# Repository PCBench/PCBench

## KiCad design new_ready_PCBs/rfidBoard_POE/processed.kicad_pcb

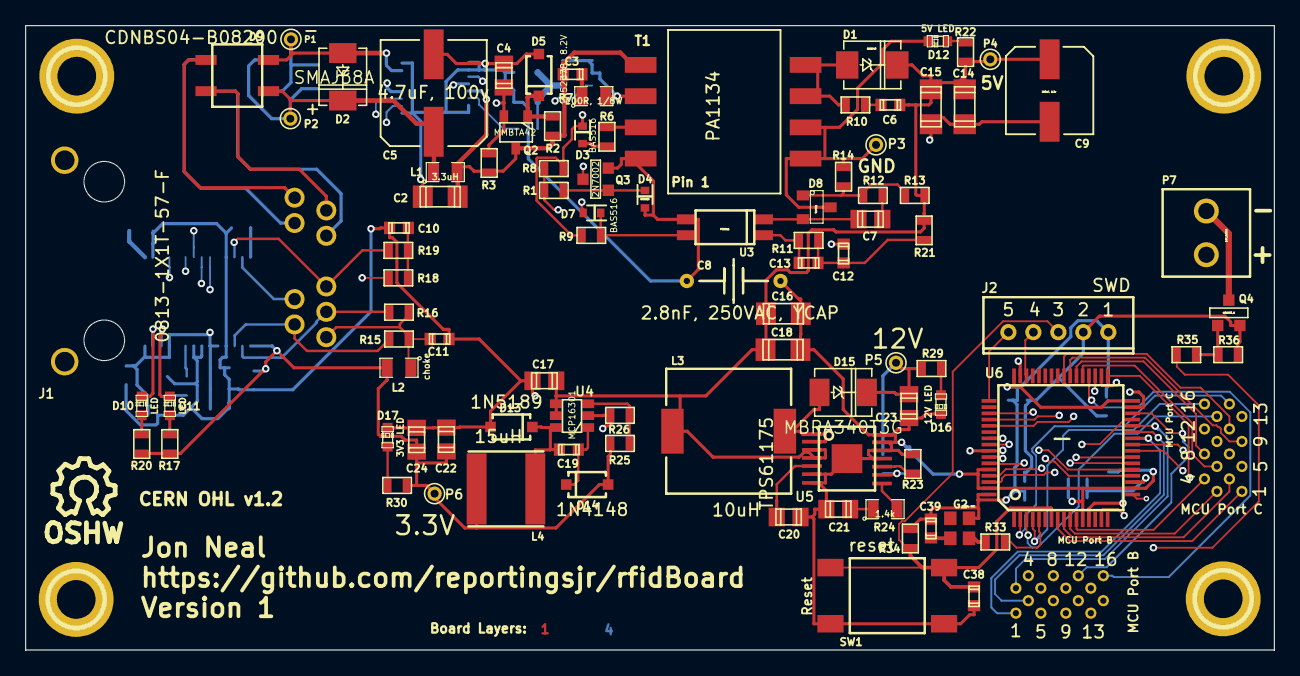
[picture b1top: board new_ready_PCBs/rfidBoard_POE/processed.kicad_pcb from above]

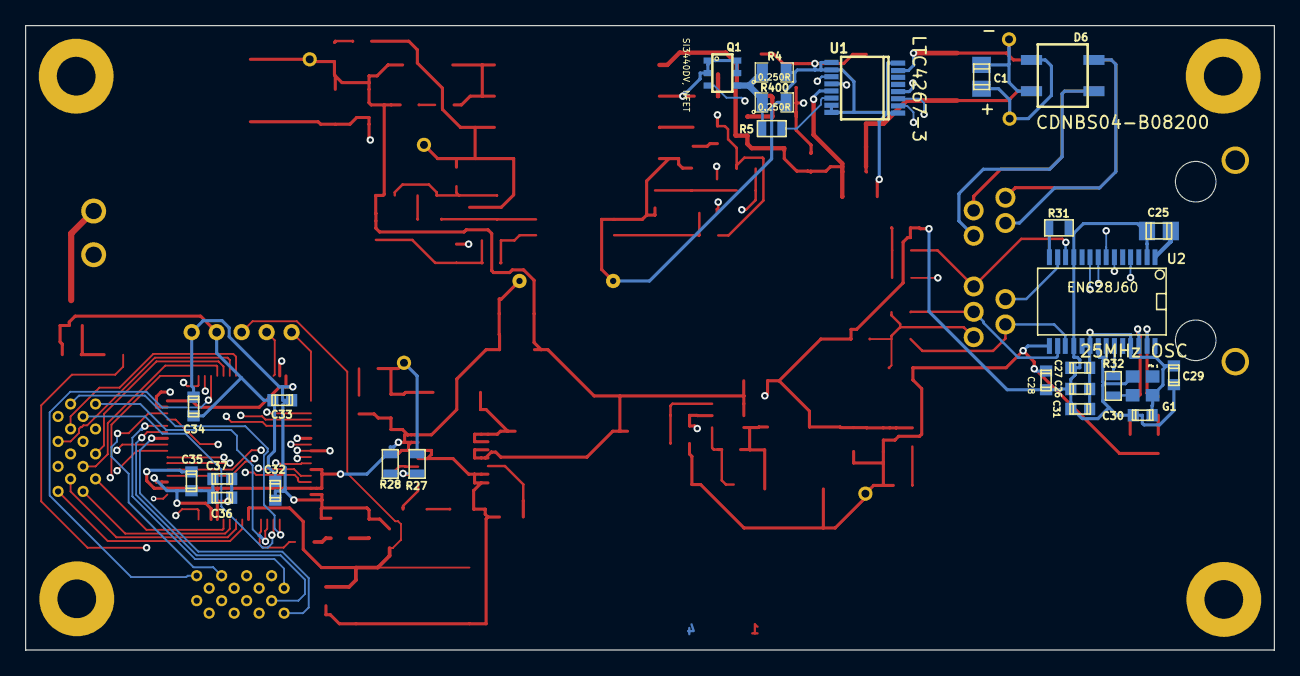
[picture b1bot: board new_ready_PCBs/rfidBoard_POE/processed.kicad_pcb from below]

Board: 4 copper layers, 100.0 x 50.0 mm, 127 parts (26 on the bottom side), 104 nets.

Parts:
1PIN, 1PIN_2, 1PIN_3, 1PIN_4: P***; 1pin
C1: 0.1uF, 100V, X7R; c_0805
C2: 1uF, 100V; c_1206
C3: 68pF, 200V; c_0603
C4: 4.7uF, 10V; c_0805
C5: 4.7uF, 100v; EEE-2AA4R7UP
C6: 470pF; c_0603
C7: 27nF; c_0805
C8: 2.8nF, 250VAC, YCAP; kemet_C900
C9: 220uF, 6.3v; EEE-FK0J221P
C10, C11: 10nF; c_0603
C12, C31, C37: 1uF; c_0603
C13: 33nF; c_0603
C14, C15: 100uF, 6.3V, X5R; c_1206
C16, C18: 10uF; c_1206
C17, C22, C24, C25: 10uF; c_0805
C19, C26, C27, C28, C29, C30, C32, C33, C34, C35, C36, C38, C39: 100nF; c_0603
C20: 47nF; c_0805
C21: 180nF; c_0805
C23: 22uF; c_0805
D1: SMB540; DO-214-AA_SMB
D2: SMAJ58A; DO-214-AC_SMA
D3, D4, D7: BAS516; SOD-523
D5: 1N5237B, 8.2V; SOD-123
D6, D9: CDNBS04-B08200; CDNBS04
D8: TLV431; SOT-23
D10, D11: LED; LED-0603
D12: 5V LED; LED-0603
D13: 1N5189; SOD-123
D14: 1N4148; SOD-123
D15: MBRA340T3G; DO-214-AC_SMA
D16: 12V LED; LED-0603
D17: 3V3 LED; LED-0603
G1: 25MHz OSC; Si501_2.5x2
G2: 24MHz OSC; Si501_2.5x2
J1: 0813-1X1T-57-F
J2: SWD; JST_PH_5pin
J3: MCU Port B; 16_pin_breakout
J4: MCU Port C; 16_pin_breakout
L1: 3.3uH; SMD-0805
L2: choke; SMD-0805
L3: 10uH; SRU1048
L4: 15uH; NR6028
P1: PoE-; PINTST
P2: PoE+; PINTST
P3: GND; PINTST
P4: +5V; PINTST
P5: +12V; PINTST
P6: +3V3; PINTST
P7: 12V_Switch; SIL2-3.5mm
Q1: SI3440DV, NFET; TSOP-6
Q2: MMBTA42; SOT-23_Inv2
Q3: 2N7002; SOT-23-GDS
Q4: MOSFET_N; SOT-23-GDS
R1, R26, R29, R36: 10k; SMD-0603
R2, R3: 220K; SMD-0603
R4, R400: 0.250R; SMD-0805
R5: 4.7K; SMD-0603
R6: 510R; SMD-0603
R7: 100R, 1/8W; SMD-0805
R8: 100k; SMD-0603
R9: 6.8k; SMD-0603
R10: 10R; SMD-0603
R11, R17, R20: 1k; SMD-0603
R12: 47k; SMD-0603
R13: 100k, 1%; SMD-0603
R14: 33.2k; SMD-0603
R15, R16, R18, R19: 49R9; SMD-0603
R21, R35: 470R; SMD-0603
R22, R30: 2.8k; SMD-0603
R23: 226k; SMD-0603
R24: 1.4k; SMD-0805
R25: 31.2k; SMD-0603
R27: 143k; SMD-0603
R28: 16.2k; SMD-0603
R31: 2.32k; SMD-0603
R32, R33: 24.9; SMD-0603
R34: 4.7k; SMD-0603
SW1: reset; TE-Switch-FSM-JSM
SYM: Symbol_OSHW-Logo_SilkScreen_07Jul2012; Symbol_OSHW-Logo_SilkScreen
T1: PA1134
U1: LTC4267-3; SSOP-16
U2: ENC28J60; SSOP-28
U3: PS2811; SSOP-4
U4: MCP16301; SOT-23-6
U5: TPS61175; HTSSOP-14-1EP
U6: STM32F100RC; LQFP64

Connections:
3V3: C22.1, C24.1, C26.1, C27.1, C28.1, C29.1, C30.2, C31.1, C32.1, C33.1, C34.1, C35.1, C36.1, C37.1, C39.2, D14.1, G1.4, G2.4, J2.1, L2.2, L4.2, P6.1, R17.2, R20.2, R25.1, R30.1, R34.2, U2.15, U2.19, U2.20, U2.25, U2.28, U6.13, U6.19, U6.32, U6.48, U6.64
5VPoE: C6.1, C9.1, C14.1, C15.1, C16.1, C17.1, C18.1, D1.2, L3.1, P4.1, R13.1, R21.2, R22.1, U4.4, U4.5, U5.3, U5.4
12V: C23.1, D15.2, P5.1, P7.1, R27.1, R29.1
/12VSwitch: R35.2, U6.15
/Ethernet+: D6.3, J1.10
/Ethernet-: D6.2, J1.5
/EthernetCS: U2.9, U6.20
/EthernetINT: U2.4, U6.17
/EthernetSCK: U2.8, U6.21
/EthernetSI: U2.7, U6.23
/EthernetSO: U2.6, U6.22
/EthernetSpare+: D9.3, J1.6
/EthernetSpare-: D9.2, J1.11
/PB0: J3.1, U6.26
/PB1: J3.2, U6.27
/PB2: J3.3, U6.28
/PB3: J3.4, U6.55
/PB4: J3.5, U6.56
/PB5: J3.6, U6.57
/PB6: J3.7, U6.58
/PB7: J3.8, U6.59
/PB8: J3.9, U6.61
/PB9: J3.10, U6.62
/PB10: J3.11, U6.29
/PB11: J3.12, U6.30
/PB12: J3.13, U6.33
/PB13: J3.14, U6.34
/PB14: J3.15, U6.35
/PB15: J3.16, U6.36
/PC0: J4.1, U6.8
/PC1: J4.2, U6.9
/PC2: J4.3, U6.10
/PC3: J4.4, U6.11
/PC4: J4.5, U6.24
/PC5: J4.6, U6.25
/PC6: J4.7, U6.37
/PC7: J4.8, U6.38
/PC8: J4.9, U6.39
/PC9: J4.10, U6.40
/PC10: J4.11, U6.51
/PC11: J4.12, U6.52
/PC12: J4.13, U6.53
/PC13: J4.14, U6.2
/PC14: J4.15, U6.3
/PC15: J4.16, U6.4
/PVcc: C4.2, D3.2, Q2.1, R3.2, R8.2, R9.1, U1.4
/TPIN+: J1.2, R18.2, U2.13
/TPIN-: J1.9, R19.2, U2.12
/TPOUT+: J1.1, R15.2, U2.17
/TPOUT-: J1.8, R16.2, U2.16
/nRST: C38.2, J2.3, R34.1, SW1.1, SW1.2, U6.7
GND: C8.2, C9.2, C10.2, C11.2, C12.2, C14.2, C15.2, C16.2, C17.2, C18.2, C20.2, C21.2, C22.2, C23.2, C24.2, C25.1, C26.2, C27.2, C28.2, C29.2, C30.1, C31.2, C32.2, C33.2, C34.2, C35.2, C36.2, C37.2, C38.1, D8.3, D12.2, D13.1, D16.2, D17.2, G1.2, J2.2, P3.1, Q4.S, R14.2, R23.2, R26.2, R28.2, R31.1, R36.2, SW1.3, SW1.4, T1.7, T1.8, U2.2, U2.11, U2.18, U2.21, U2.22, U4.2, U5.6, U5.7, U5.11, U5.12, U5.13, U5.14, U5.15, U6.12, U6.18, U6.31, U6.47, U6.60, U6.63
GNDA: C2.2, C4.1, C5.2, C8.1, D4.1, D5.1, J1.12, Q3.S, R4.2, R400.2, T1.1, U1.1, U1.8, U1.9, U1.10, U1.15, U1.16, U3.3
unnamed: C1.1, C5.1, D2.2, D6.1, D9.1, L1.1, P2.1
unnamed: C1.2, D2.1, D6.4, D9.4, P1.1, U1.7, U1.12
unnamed: C2.1, C3.1, L1.2, Q2.3, R2.1, R3.1, T1.4, U1.13
unnamed: C3.2, R7.1
unnamed: C6.2, R10.2
unnamed: C7.1, R12.1
unnamed: C7.2, D8.2, U3.2
unnamed: C10.1, R18.1, R19.1
unnamed: C11.1, J1.7, L2.1, R15.1, R16.1
unnamed: C12.1, C13.1, R11.1, R21.1
unnamed: C13.2, R11.2, U3.1
unnamed: C19.1, D14.2, U4.1
unnamed: C19.2, D13.2, L4.1, U4.6
unnamed: C20.1, U5.5
unnamed: C21.1, R24.1
unnamed: C25.2, U2.1
unnamed: C39.1, G2.2
unnamed: D1.1, R10.1, T1.5, T1.6
unnamed: D3.1, R6.1
unnamed: D4.2, Q3.G, R1.2
unnamed: D5.2, Q2.2, R2.2
unnamed: D7.1, Q3.D, U1.2
unnamed: D7.2, R9.2, U3.4
unnamed: D8.1, R12.2, R13.2, R14.1
unnamed: D10.1, R20.1
unnamed: D10.2, U2.27
unnamed: D11.1, R17.1
unnamed: D11.2, U2.26
unnamed: D12.1, R22.2
unnamed: D15.1, L3.2, U5.1, U5.2
unnamed: D16.1, R29.2
unnamed: D17.1, R30.2
unnamed: G1.3, R32.1
unnamed: G2.3, R33.1
unnamed: J2.4, U6.46
unnamed: J2.5, U6.49
unnamed: P7.2, Q4.D
unnamed: Q1.1, Q1.2, Q1.5, Q1.6, R7.2, T1.3
unnamed: Q1.3, U1.3
unnamed: Q1.4, R4.1, R5.2, R400.1
unnamed: Q4.G, R35.1, R36.1
unnamed: R1.1, R8.1, U1.11
unnamed: R5.1, U1.14
unnamed: R6.2, T1.2
unnamed: R23.1, U5.10
unnamed: R24.2, U5.8
unnamed: R25.2, R26.1, U4.3
unnamed: R27.2, R28.1, U5.9
unnamed: R31.2, U2.14
unnamed: R32.2, U2.23
unnamed: R33.2, U6.5

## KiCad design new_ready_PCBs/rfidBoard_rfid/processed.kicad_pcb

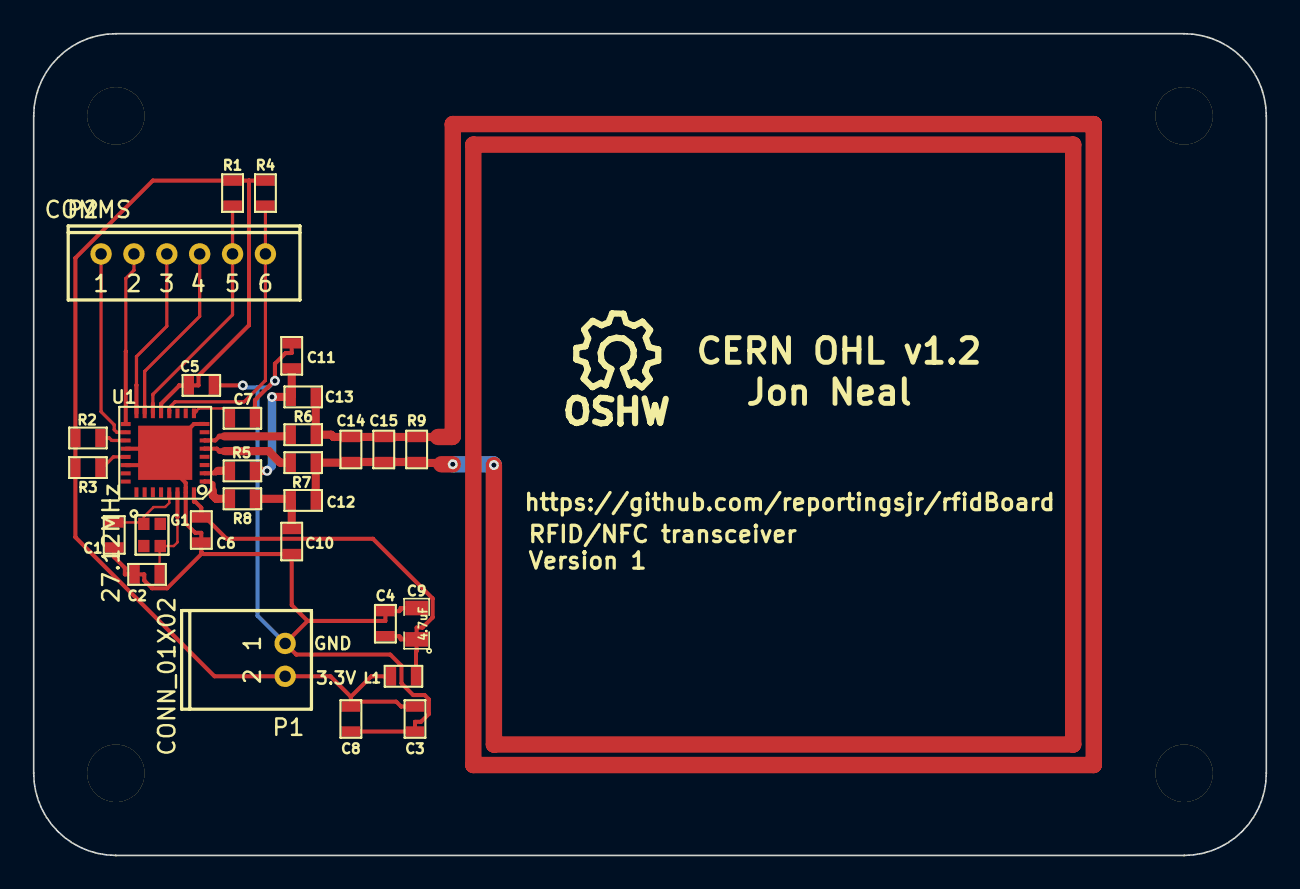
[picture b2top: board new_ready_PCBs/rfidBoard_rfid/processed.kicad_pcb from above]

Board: 2 copper layers, 75.0 x 50.0 mm, 34 parts (0 on the bottom side), 21 nets.

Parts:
C1, C2: 4pF; SMD-0603
C3, C4: 10nF; SMD-0603
C5, C6: 100nF; SMD-0603
C7: 1nF; SMD-0603
C8: 1uF; SMD-0603
C9: 4.7uF; SMD-0805
C10, C11: open; SMD-0603
C12, C13: 150pF; SMD-0603
C14: 220pF; SMD-0603
C15: 15pF; SMD-0603
G1: 27.12MHz; 2x1.6_crystal
L1: tx_3v3_choke; SMD-0603
MH: MountingHole_3-5mm_RevA_Date21Jun2010; MountingHole_3-5mm
MH_2, MH_3, MH_4: MountingHole_3-5mm_RevA_Date21Jun2010; MountingHole_3-5mm
P1: CONN_01X02; JST_PH_2pin_side
P2: COMMS; JST_PH_6pin
R1, R2, R3, R4: 3.3k; SMD-0603
R5, R8: 0; SMD-0603
R6, R7: 330; SMD-0603
R9: 2.26k; SMD-0603
SYM: Symbol_OSHW-Logo_SilkScreen_07Jul2012; Symbol_OSHW-Logo_SilkScreen
U1: CR95HF; QFN-32-1EP

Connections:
3V3: C3.1, C5.1, C8.1, L1.1, P1.2, R1.1, R2.2, R3.2, R4.1, U1.13
3V3_RF: C4.1, C6.1, C9.1, L1.2, U1.32
GND: C1.2, C2.2, C3.2, C4.2, C5.2, C6.2, C7.2, C8.2, C9.2, C10.1, C11.1, P1.1, U1.8, U1.20, U1.22, U1.31, U1.33
unnamed: C1.1, G1.1, U1.29
unnamed: C2.1, G1.3, U1.30
unnamed: C7.1, U1.9
unnamed: C10.2, C12.2, R8.1
unnamed: C11.2, C13.2, R5.1
unnamed: C12.1, C13.1, C14.1, C14.2, C15.1, C15.2, R6.1, R7.1, R9.1, R9.2
unnamed: P2.1, U1.18
unnamed: P2.2, U1.17
unnamed: P2.3, U1.16
unnamed: P2.4, U1.15
unnamed: P2.5, R1.2, U1.14
unnamed: P2.6, R4.2, U1.12
unnamed: R2.1, U1.19
unnamed: R3.1, U1.21
unnamed: R5.2, U1.2
unnamed: R6.2, U1.6
unnamed: R7.2, U1.5
unnamed: R8.2, U1.1

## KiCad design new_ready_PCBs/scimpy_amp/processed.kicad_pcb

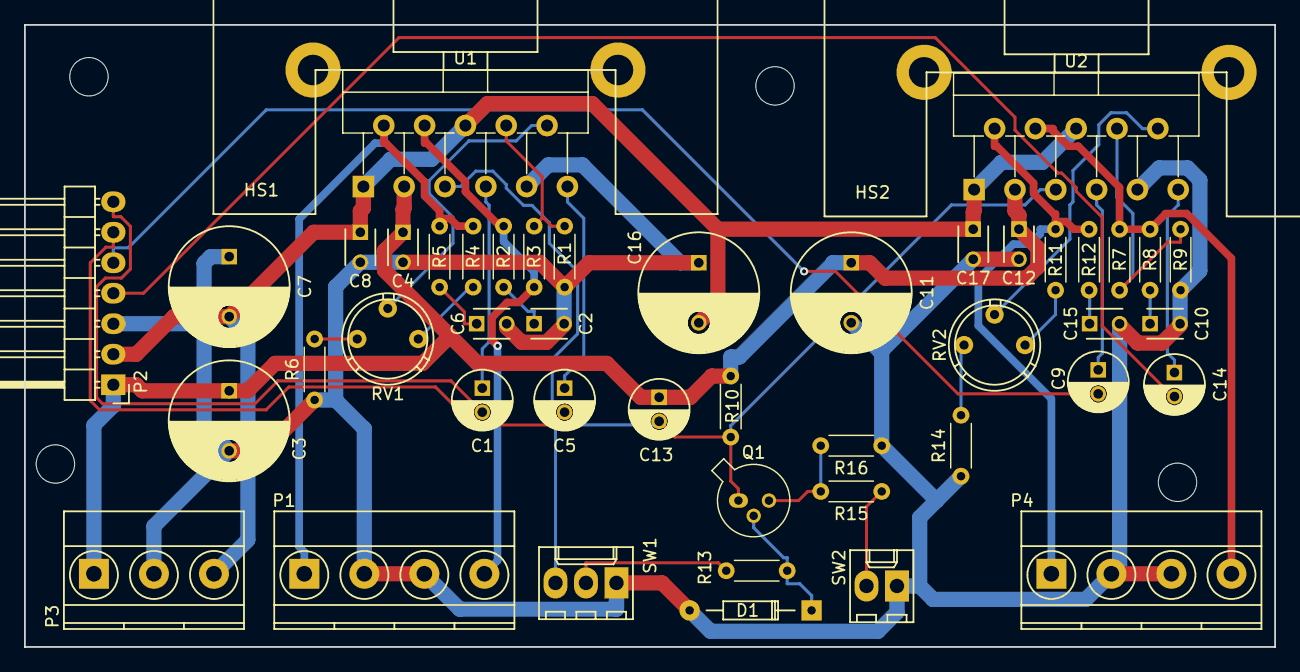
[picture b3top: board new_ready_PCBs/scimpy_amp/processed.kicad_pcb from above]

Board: 2 copper layers, 104.1 x 51.8 mm, 47 parts (0 on the bottom side), 32 nets.

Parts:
C1, C5, C9, C14: 1u-audio; C_Radial_D5_L11_P2
C2, C4, C6, C8, C10, C12, C15, C17: 100n; C_Disc_D3_P2.5
C3, C7, C11, C16: 1000u; C_Radial_D10_L20_P5
C13: 1u; C_Radial_D5_L11_P2
D1: 5.1V; Diode_DO-35_SOD27_Horizontal_RM10
HS1, HS2: multiwatt11_heatsink
P1, P4: CONN_01X04; TerminalBlock_Pheonix_MKDS1.5-4pol
P2: CONN_01X07; Pin_Header_Angled_1x07
P3: CONN_01X03; TerminalBlock_Pheonix_MKDS1.5-3pol
Q1: BC107; TO-18-3
R1, R7: 18K; R_Axial_DIN0204_L3.6mm_D1.6mm_P5.08mm_Horizontal
R2, R5, R8, R12: 4.8R; R_Axial_DIN0204_L3.6mm_D1.6mm_P5.08mm_Horizontal
R3, R9: 560R; R_Axial_DIN0204_L3.6mm_D1.6mm_P5.08mm_Horizontal
R4, R11: 68K; R_Axial_DIN0204_L3.6mm_D1.6mm_P5.08mm_Horizontal
R6, R14: 1K5; R_Axial_DIN0204_L3.6mm_D1.6mm_P5.08mm_Horizontal
R10, R15: 15K; R_Axial_DIN0204_L3.6mm_D1.6mm_P5.08mm_Horizontal
R13: 10K; R_Axial_DIN0204_L3.6mm_D1.6mm_P5.08mm_Horizontal
R16: 47K; R_Axial_DIN0204_L3.6mm_D1.6mm_P5.08mm_Horizontal
RV1, RV2: 1K POT; Potentiometer_Bourns_3339P_Angular_ScrewUp
SW1: Standby; Molex_KK-6410-03_03x2.54mm_Straight
SW2: Mute; Molex_KK-6410-02_02x2.54mm_Straight
U1, U2: TDA7292; Multiwatt-11_Vertical_StaggeredType1

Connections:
+15V: C3.1, C4.1, C11.1, C12.1, C13.1, P2.1, P3.1, R10.2, U1.3, U2.3
-15V: C7.2, C8.1, C16.2, C17.1, P2.2, P3.3, U1.1, U1.6, U2.1, U2.6
/M/SB: C13.2, Q1.1, R10.1, SW1.3, U1.5, U2.5
/left_high_in: C9.2, P2.5
/left_high_out: P4.4, R7.2, R8.2, U2.4
/left_low_in: C14.2, P2.4
/left_low_out: P4.1, R11.2, R12.2, U2.2
/right_high_in: C1.2, P2.7
/right_high_out: P1.4, R1.2, R2.2, U1.4
/right_low_in: C5.2, P2.6
/right_low_out: P1.1, R4.2, R5.2, U1.2
GND: C2.2, C3.2, C4.2, C6.2, C7.1, C8.2, C10.2, C11.2, C12.2, C15.2, C16.1, C17.2, D1.2, P1.2, P1.3, P2.3, P3.2, P4.2, P4.3, R3.1, R6.1, R9.1, R14.1, R16.1, SW1.1, SW2.1, U1.9, U2.9
unnamed: C1.1, U1.7
unnamed: C2.1, R2.1
unnamed: C5.1, U1.11
unnamed: C6.1, R5.1
unnamed: C9.1, U2.7
unnamed: C10.1, R8.1
unnamed: C14.1, U2.11
unnamed: C15.1, R12.1
unnamed: D1.1, Q1.2, R13.2
unnamed: Q1.3, R15.2, R16.2
unnamed: R1.1, R3.2, U1.8
unnamed: R4.1, RV1.3
unnamed: R6.2, RV1.1
unnamed: R7.1, R9.2, U2.8
unnamed: R11.1, RV2.3
unnamed: R13.1, SW1.2
unnamed: R14.2, RV2.1
unnamed: R15.1, SW2.2
unnamed: RV1.2, U1.10
unnamed: RV2.2, U2.10

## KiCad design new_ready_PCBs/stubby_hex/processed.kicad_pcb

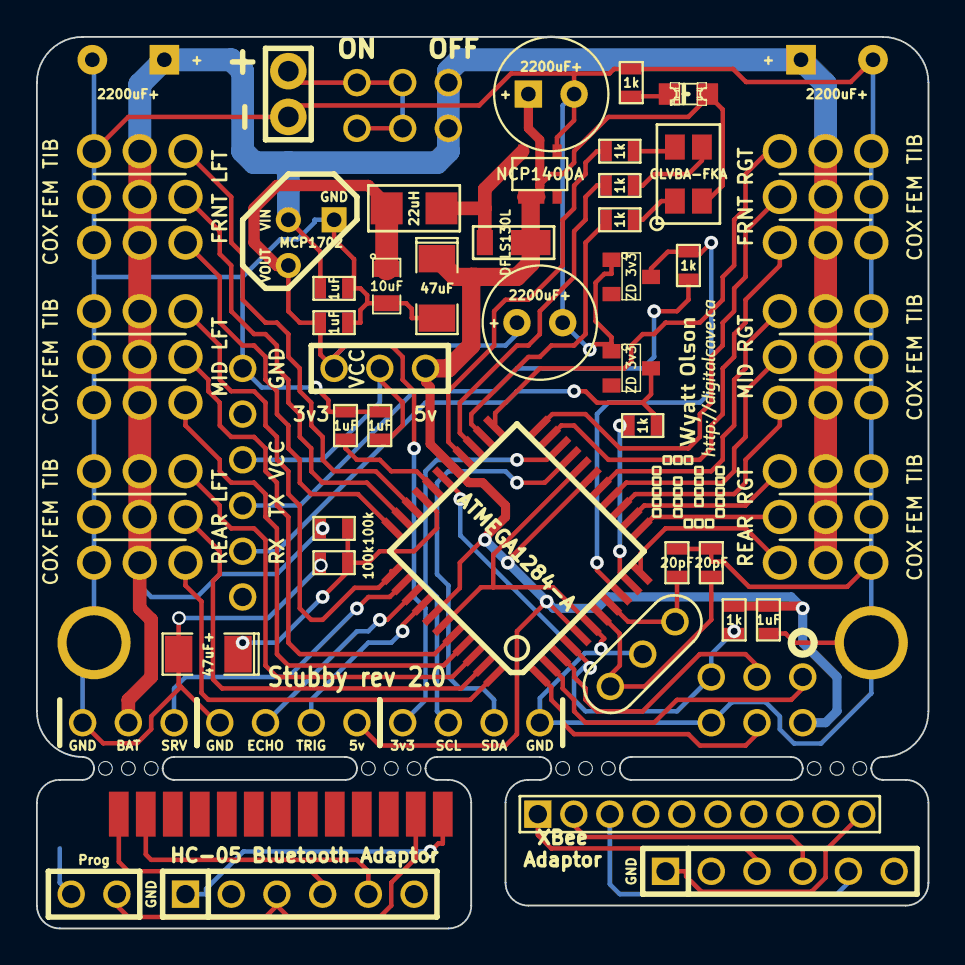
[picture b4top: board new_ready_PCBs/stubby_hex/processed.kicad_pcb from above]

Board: 2 copper layers, 49.5 x 49.5 mm, 60 parts (1 on the bottom side), 58 nets.

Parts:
1PIN, 1PIN_2: P***; 1pin
C1, C8: 2200uF+; C1V7
C2, C3, C9, C13, C14: 1uF; SM0603_VALUE
C4, C5: 2200uF+; C1V8
C6: 10uF; SM0805
C7: 47uF; SM1206POL
C10: 47uF+; SM1206POL
C11, C12: 20pF; SM0603_VALUE
D1: DFLS130L; POWERDI_123
D2: LED; LED-0805-MARKED_ANODE
D3: CLVBA-FKA; 4-PLCC
IC1: ATMEGA1284-A; TQFP44
JP1: CONN_3; SIL-3
L1: 22uH; SM1007
P1: BATT (4.8V-6V); SIL-2
P2: PROG; ISP
P3: CONN_10; SIL-10
P4, P6, P8: CONN_6; SIL-6
P5: CONN_13; HC05_Edge
P7: CONN_1; SIL-1
P9: CONN_2; SIL-2
P10, P11: CONN_4; SIL-4
R1, R4, R5, R6, R7, R8, R9: 1k; SM0603_VALUE
R2, R3: 100k; SM0603_VALUE
S1: FRNT LFT; HEX_LEG
S2: FRNT RGT; HEX_LEG_REVERSE
S3: MID LFT; HEX_LEG
S4: MID RGT; HEX_LEG_REVERSE
S5: REAR LFT; HEX_LEG
S6: REAR RGT; HEX_LEG_REVERSE
S7: CONN_3; SIL-3
SW1: DPDT
VAL: DIGITALCAVE_LOGO_WIDE_SMALL
VR1: MCP1702; TO92
VR2: NCP1400A; SOT23-5
X1: CRYSTAL_RESONATOR
ZD1, ZD2: ZD 3v3; SOT23
mouse_bites: VAL**; mouse_bites
mouse_bites_2, mouse_bites_3, mouse_bites_4: VAL**; mouse_bites

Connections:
+3.3V: C1.1, C2.1, C6.1, JP1.3, L1.1, P10.1, VR1.3
+5V: C7.1, C8.1, C9.2, D1.2, D2.1, D3.2, IC1.5, IC1.17, IC1.27, IC1.38, JP1.1, P2.2, P11.1, R4.1, VR2.1, VR2.2
+BATT: C3.1, C4.1, C5.1, R2.1, S1.4, S1.5, S1.6, S2.4, S2.5, S2.6, S3.4, S3.5, S3.6, S4.4, S4.5, S4.6, S5.4, S5.5, S5.6, S6.4, S6.5, S6.6, S7.2, SW1.3, SW1.6, VR1.2
/ADC_BATTERY_METER: C10.1, IC1.30, R2.2, R3.2
/AREF: C13.2, IC1.29
/AVR_RX: IC1.9, R9.1, ZD1.2
/AVR_TX: IC1.10, R8.1
/BATTERY: P1.1, SW1.1, SW1.2, SW1.4, SW1.5
/BLUETOOTH_GND: P5.13, P8.1
/DIST_ECHO: IC1.36, P11.3
/DIST_SERVO: IC1.35, S7.3
/DIST_TRIG: IC1.37, P11.2
/I2C_SCL: IC1.19, P10.3
/I2C_SDA: IC1.20, P10.2
/LED_BL: IC1.25, R6.1
/LED_BL_R: D3.3, R6.2
/LED_GR: IC1.26, R5.1
/LED_GR_R: D3.4, R5.2
/LED_RD: IC1.24, R7.1
/LED_RD_R: D3.1, R7.2
/MISO: IC1.2, P2.1
/MOSI: IC1.1, P2.4
/PWM00: IC1.33, S1.1
/PWM01: IC1.32, S1.2
/PWM02: IC1.31, S1.3
/PWM03: IC1.23, S2.1
/PWM04: IC1.22, S2.2
/PWM05: IC1.21, S2.3
/PWM06: IC1.41, S3.1
/PWM07: IC1.40, S3.2
/PWM08: IC1.34, S3.3
/PWM09: IC1.16, S4.1
/PWM10: IC1.15, S4.2
/PWM11: IC1.14, S4.3
/PWM12: IC1.44, S5.1
/PWM13: IC1.43, S5.2
/PWM14: IC1.42, S5.3
/PWM15: IC1.13, S6.1
/PWM16: IC1.12, S6.2
/PWM17: IC1.11, S6.3
/RESET: IC1.4, P2.5, R4.2
/SCK: IC1.3, P2.3
/XBEE_GND: P3.10, P4.1
/XTAL1: C12.2, IC1.8, X1.1
/XTAL2: C11.2, IC1.7, X1.2
GND: 1PIN.1, 1PIN_2.1, C1.2, C2.2, C3.2, C4.2, C5.2, C6.2, C7.2, C8.2, C9.1, C10.2, C11.1, C12.1, C13.1, C14.1, IC1.6, IC1.18, IC1.28, IC1.39, P1.2, P2.6, P6.1, P10.4, P11.4, R1.2, R3.1, S1.7, S1.8, S1.9, S2.7, S2.8, S2.9, S3.7, S3.8, S3.9, S4.7, S4.8, S4.9, S5.7, S5.8, S5.9, S6.7, S6.8, S6.9, S7.1, VR1.1, VR2.4, X1.3, ZD1.1, ZD2.1
unnamed: P5.2, P8.5
unnamed: P5.1, P8.4
unnamed: P3.3, P4.5
unnamed: D1.1, L1.2, VR2.5
unnamed: P7.1, P9.1
unnamed: P5.12, P8.3, P9.2
unnamed: P3.2, P4.4
unnamed: P3.1, P4.3
unnamed: P6.4, R9.2
unnamed: P6.5, R8.2, ZD2.2
unnamed: C14.2, JP1.2, P6.3
unnamed: D2.2, R1.1

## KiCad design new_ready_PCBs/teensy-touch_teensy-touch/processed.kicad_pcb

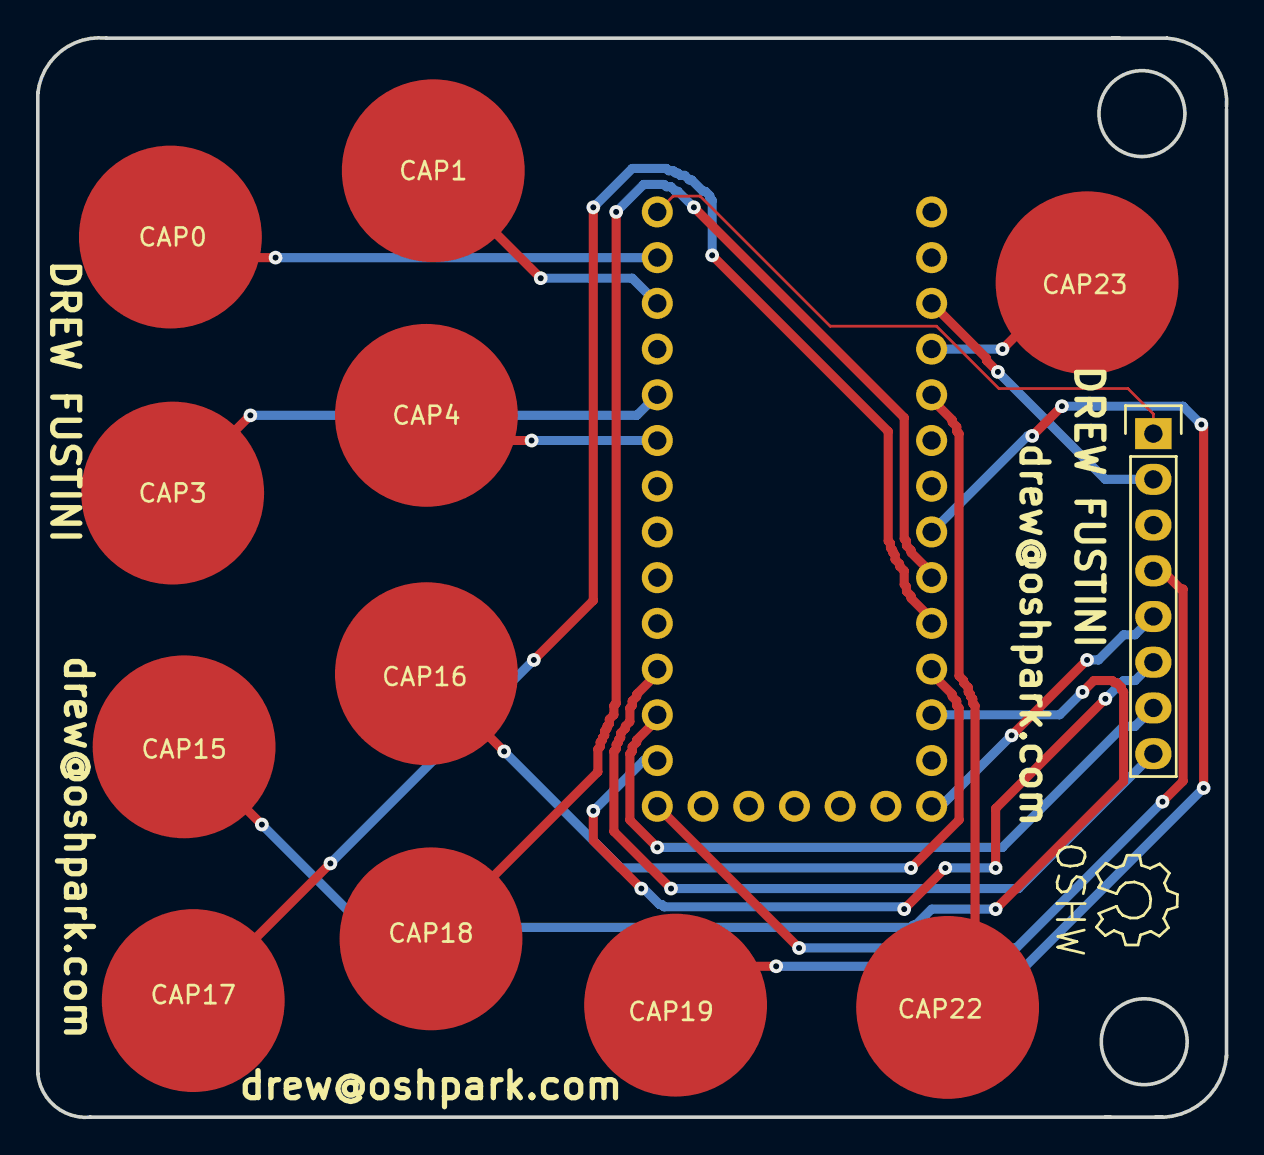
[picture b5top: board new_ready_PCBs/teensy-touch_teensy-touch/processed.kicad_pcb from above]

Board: 2 copper layers, 66.0 x 60.0 mm, 13 parts (0 on the bottom side), 18 nets.

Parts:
CAP0, CAP1, CAP3, CAP4, CAP15, CAP16, CAP17, CAP18, CAP19, CAP22, CAP23: CAPSENSE_CIRCLE; CAPSENSE_CIRCLE_D10
J1: TEENSY-LC
J2: OLED_128x64; Pin_Header_Straight_1x08

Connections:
/CAP15: CAP15.1, J1.15
/CAP16: CAP16.1, J1.16
/CAP17: CAP17.1, J1.17
/CAP18: CAP18.1, J1.18
/CAP19: CAP19.1, J1.19
/CAP22: CAP22.1, J1.22
/CAP23: CAP23.1, J1.23
/CLK: J1.10, J2.7
/CS: J1.12, J2.4
/DC: J1.11, J2.6
/Data: J1.9, J2.8
/GND: J1.G1, J2.1
/RST: J1.13, J2.5
/VIN: J1.3V2, J2.2
unnamed: CAP0.1, J1.0
unnamed: CAP1.1, J1.1
unnamed: CAP3.1, J1.3
unnamed: CAP4.1, J1.4

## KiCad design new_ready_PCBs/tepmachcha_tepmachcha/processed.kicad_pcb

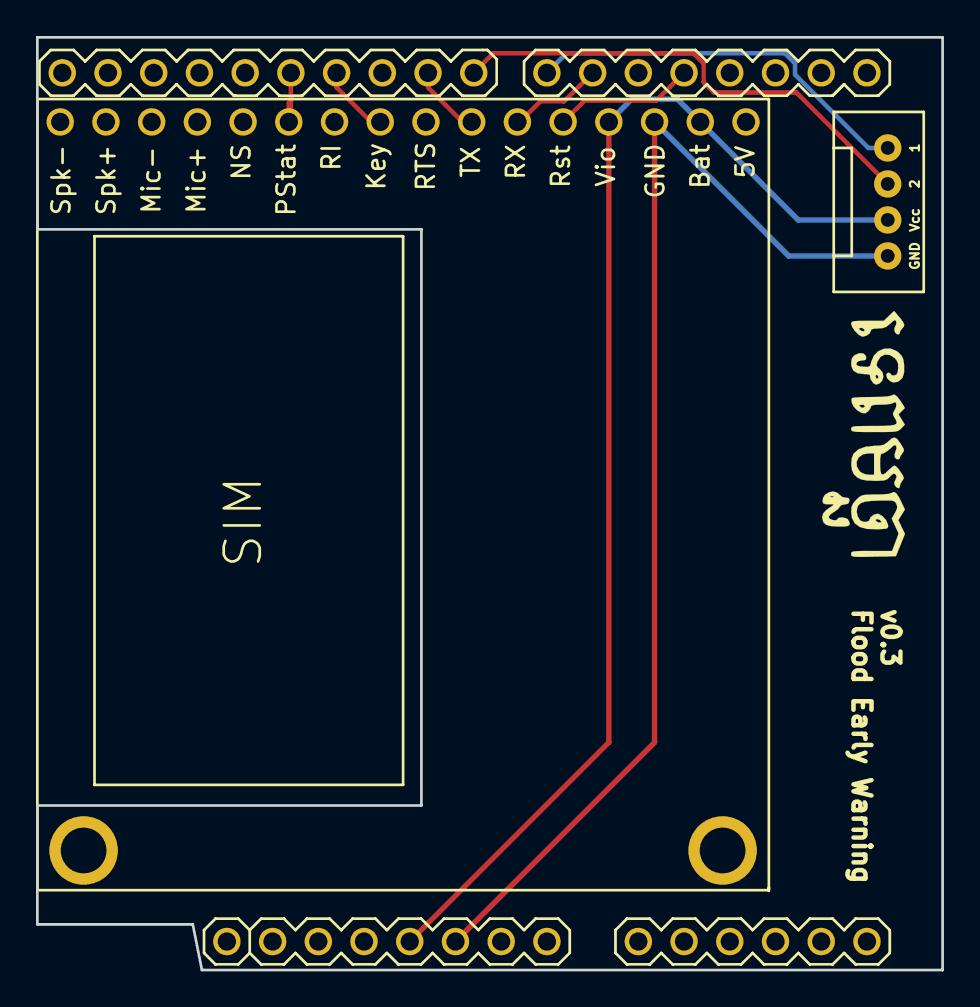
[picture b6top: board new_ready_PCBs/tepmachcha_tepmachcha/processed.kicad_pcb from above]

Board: 2 copper layers, 50.3 x 51.8 mm, 3 parts (0 on the bottom side), 9 nets.

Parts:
P1: CONN_01X04; Grove_straight
SHIELD1: ARDUINO_SHIELD; ARDUINO
U1: FONA_808

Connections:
GND: P1.4, SHIELD1.GND1, U1.3
unnamed: P1.1, SHIELD1.7
unnamed: P1.2, SHIELD1.8
unnamed: SHIELD1.4, U1.5
unnamed: SHIELD1.6, U1.6
unnamed: SHIELD1.9, U1.7
unnamed: SHIELD1.11, U1.9
unnamed: SHIELD1.12, U1.11
VCC: P1.3, SHIELD1.5V, U1.2, U1.4

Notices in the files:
new_ready_PCBs/rfidBoard_POE/processed.kicad_pcb:
CERN OHL v1.2
